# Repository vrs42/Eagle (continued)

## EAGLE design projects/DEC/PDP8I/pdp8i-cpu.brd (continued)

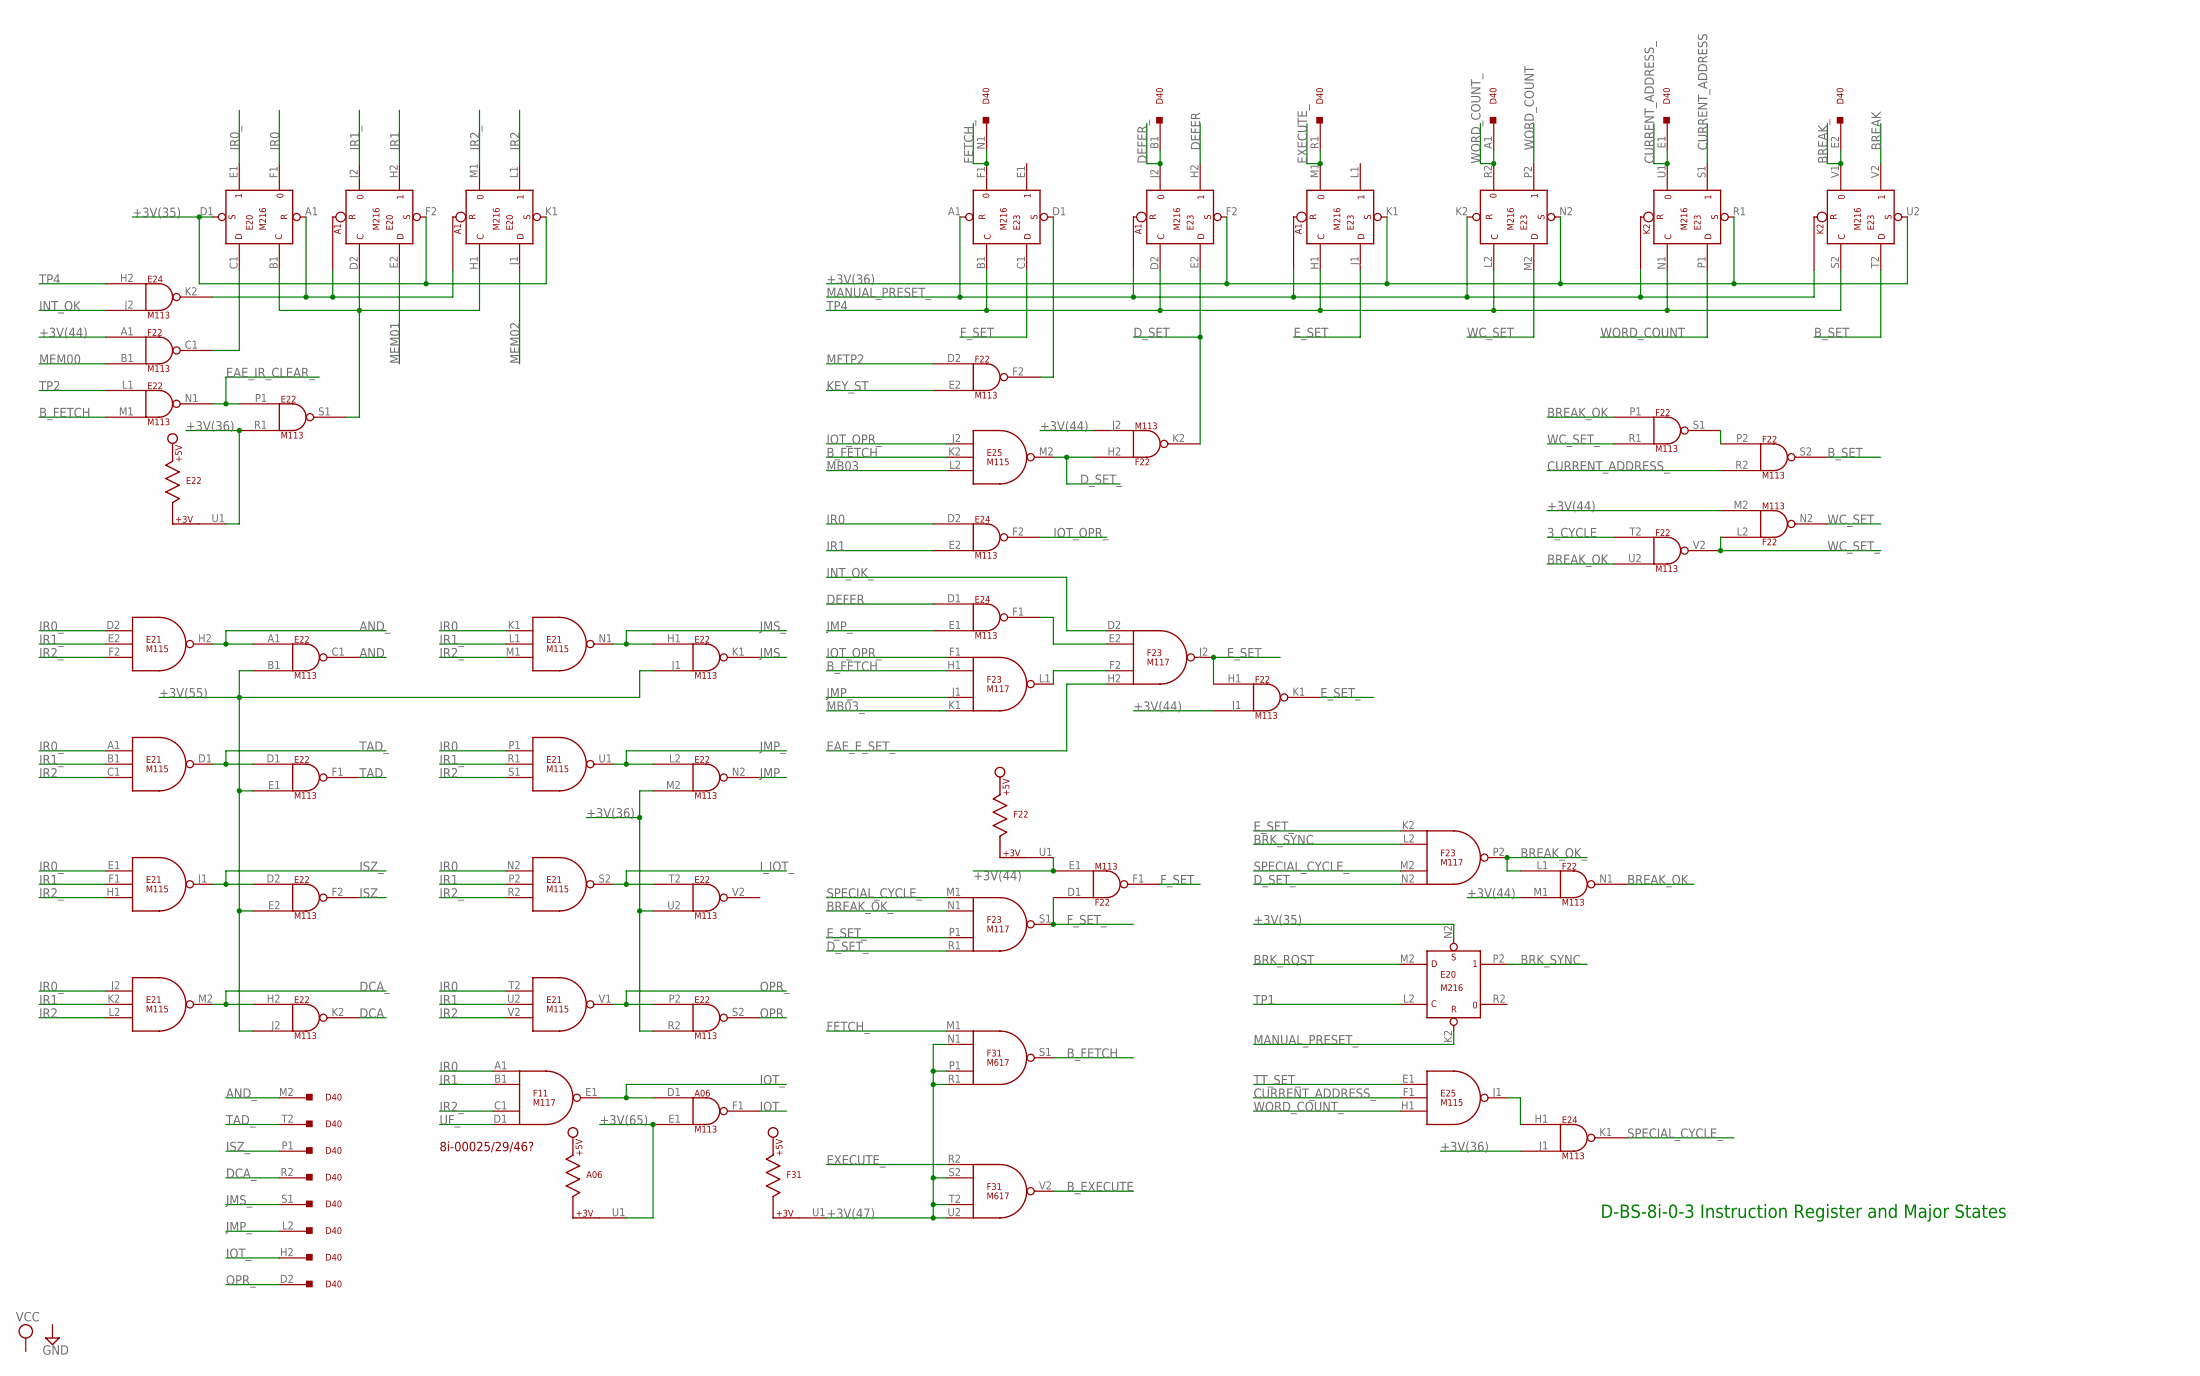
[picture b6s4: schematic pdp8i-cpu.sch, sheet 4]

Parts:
A06: M113; H807
D40: M900; H807
E20, E23: M216; H807
E21, E25: M115; H807
E22, E24: M113; H807
F11, F23: M117; H807
F22: M113; H807
F31: M617; H807

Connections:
3_CYCLE: F22.T2 (IN1); also elsewhere on the board
+3V(35): E20.D1 (S), E20.F2 (S), E20.K1 (S), E20.N2 (S); also elsewhere on the board
+3V(36): E22.M2 (IN2), E22.R1 (IN2), E22.R2 (IN2), E22.U1, E22.U2 (IN2), E23.F2 (S), E23.K1 (S), E23.N2 (S), E23.R1 (S), E23.U2 (S), E24.J1 (IN2); also elsewhere on the board
+3V(44): F22.A1 (IN1), F22.E1 (IN2), F22.J1 (IN2), F22.J2 (IN2), F22.M1 (IN2), F22.M2 (IN2), F22.U1; also elsewhere on the board
+3V(47): F31.N1 (IN2), F31.P1 (IN3), F31.R1 (IN4), F31.S2 (IN2), F31.T2 (IN3), F31.U1, F31.U2 (IN4); also elsewhere on the board
+3V(55): E22.B1 (IN2), E22.E1 (IN2), E22.E2 (IN2), E22.J1 (IN2), E22.J2 (IN2); also elsewhere on the board
+3V(65): A06.E1 (IN2), A06.U1; also elsewhere on the board
AND: E22.C1 (OUT); also elsewhere on the board
AND_: D40.M2, E21.H2 (OUT), E22.A1 (IN1); also elsewhere on the board
BREAK: E23.V2 (1); also elsewhere on the board
BREAK_: D40.E2, E23.V1 (0); also elsewhere on the board
BREAK_OK: F22.N1 (OUT), F22.P1 (IN1), F22.U2 (IN2); also elsewhere on the board
BREAK_OK_: F22.L1 (IN1), F23.N1 (IN2), F23.P2 (OUT); also elsewhere on the board
BRK_RQST: E20.M2 (D); also elsewhere on the board
BRK_SYNC: E20.P2 (1), F23.L2 (IN2)
B_EXECUTE: F31.V2 (OUT); also elsewhere on the board
B_FETCH: E22.M1 (IN2), E25.K2 (IN2), F23.H1 (IN2), F31.S1 (OUT); also elsewhere on the board
B_SET: E23.T2 (D), F22.S2 (OUT); also elsewhere on the board
CURRENT_ADDRESS: E23.S1 (1); also elsewhere on the board
CURRENT_ADDRESS_: D40.E1, E23.U1 (0), E25.F1 (IN2), F22.R2 (IN2)
DCA: E22.K2 (OUT); also elsewhere on the board
DCA_: D40.R2, E21.M2 (OUT), E22.H2 (IN1); also elsewhere on the board
DEFER: E23.H2 (1), E24.D1 (IN1); also elsewhere on the board
DEFER_: D40.B1, E23.J2 (0)
D_SET: E23.E2 (D), F22.K2 (OUT)
D_SET_: E25.M2 (OUT), F22.H2 (IN1), F23.N2 (IN4), F23.R1 (IN4); also elsewhere on the board
EAE_E_SET_: F23.H2 (IN4); also elsewhere on the board
EAE_IR_CLEAR_: E22.N1 (OUT), E22.P1 (IN1); also elsewhere on the board
EXECUTE_: D40.R1, E23.M1 (0), F31.R2 (IN1)
E_SET: E23.J1 (D), F22.H1 (IN1), F23.J2 (OUT)
E_SET_: F22.K1 (OUT), F23.K2 (IN1), F23.P1 (IN3); also elsewhere on the board
FETCH_: D40.N1, E23.F1 (0), F31.M1 (IN1); also elsewhere on the board
F_SET: E23.C1 (D), F22.F1 (OUT); also elsewhere on the board
F_SET_: F22.D1 (IN1), F23.S1 (OUT); also elsewhere on the board
GND: A06.C2 (GND), A06.T1 (GND), E20.C2 (GND), E20.T1 (GND), E21.C2 (GND), E21.T1 (GND), E22.C2 (GND), E22.T1 (GND), E23.C2 (GND), E23.T1 (GND), E24.C2 (GND), E24.T1 (GND), E25.C2 (GND), E25.T1 (GND), F11.C2 (GND), F11.T1 (GND), F22.C2 (GND), F22.T1 (GND), F23.C2 (GND), F23.T1 (GND), F31.C2 (GND), F31.T1 (GND); also elsewhere on the board
INT_OK: E24.J2 (IN2); also elsewhere on the board
INT_OK_: F23.D2 (IN1); also elsewhere on the board
IOT: A06.F1 (OUT); also elsewhere on the board
IOT_: A06.D1 (IN1), D40.H2, F11.E1 (OUT)
IOT_OPR_: E24.F2 (OUT), E25.J2 (IN1), F23.F1 (IN1)
IR0: E20.F1 (0), E21.K1 (IN1), E21.N2 (IN1), E21.P1 (IN1), E21.T2 (IN1), E24.D2 (IN1), F11.A1 (IN1)
IR0_: E20.E1 (1), E21.A1 (IN1), E21.D2 (IN1), E21.E1 (IN1), E21.J2 (IN1)
IR1: E20.H2 (1), E21.F1 (IN2), E21.K2 (IN2), E21.P2 (IN2), E21.U2 (IN2), E24.E2 (IN2), F11.B1 (IN2)
IR1_: E20.J2 (0), E21.B1 (IN2), E21.E2 (IN2), E21.L1 (IN2), E21.R1 (IN2)
IR2: E20.L1 (1), E21.C1 (IN3), E21.L2 (IN3), E21.S1 (IN3), E21.V2 (IN3)
IR2_: E20.M1 (0), E21.F2 (IN3), E21.H1 (IN3), E21.M1 (IN3), E21.R2 (IN3), F11.C1 (IN3)
ISZ: E22.F2 (OUT); also elsewhere on the board
ISZ_: D40.P1, E21.J1 (OUT), E22.D2 (IN1)
I_IOT_: E21.S2 (OUT), E22.T2 (IN1); also elsewhere on the board
JMP: E22.N2 (OUT); also elsewhere on the board
JMP_: D40.L2, E21.U1 (OUT), E22.L2 (IN1), E24.E1 (IN2), F23.J1 (IN3); also elsewhere on the board
JMS: E22.K1 (OUT); also elsewhere on the board
JMS_: D40.S1, E21.N1 (OUT), E22.H1 (IN1); also elsewhere on the board
KEY_ST: F22.E2 (IN2); also elsewhere on the board
MANUAL_PRESET_: E20.K2 (R), E23.A1 (R), E23.K2 (R); also elsewhere on the board
MB03: E25.L2 (IN3); also elsewhere on the board
MB03_: F23.K1 (IN4); also elsewhere on the board
MEM00: F22.B1 (IN2); also elsewhere on the board
MEM01: E20.E2 (D); also elsewhere on the board
MEM02: E20.J1 (D); also elsewhere on the board
MFTP2: F22.D2 (IN1); also elsewhere on the board
unnamed: E20.A1 (R), E24.K2 (OUT)
unnamed: E20.C1 (D), F22.C1 (OUT)
unnamed: E20.B1 (C), E20.D2 (C), E20.H1 (C), E22.S1 (OUT)
unnamed: E23.D1 (S), F22.F2 (OUT)
unnamed: E24.F1 (OUT), F23.E2 (IN2)
unnamed: F23.F2 (IN3), F23.L1 (OUT)
unnamed: F22.P2 (IN1), F22.S1 (OUT)
unnamed: E24.H1 (IN1), E25.J1 (OUT)
OPR: E22.S2 (OUT); also elsewhere on the board
OPR_: D40.D2, E21.V1 (OUT), E22.P2 (IN1)
SPECIAL_CYCLE_: E24.K1 (OUT), F23.M1 (IN1), F23.M2 (IN3)
TAD: E22.F1 (OUT); also elsewhere on the board
TAD_: D40.T2, E21.D1 (OUT), E22.D1 (IN1); also elsewhere on the board
TP1: E20.L2 (C); also elsewhere on the board
TP2: E22.L1 (IN1); also elsewhere on the board
TP4: E23.B1 (C), E23.D2 (C), E23.H1 (C), E23.L2 (C), E23.N1 (C), E23.S2 (C), E24.H2 (IN1); also elsewhere on the board
TT_SET_: E25.E1 (IN1); also elsewhere on the board
UF_: F11.D1 (IN4); also elsewhere on the board
VCC: A06.A2 (VCC), E20.A2 (VCC), E21.A2 (VCC), E22.A2 (VCC), E23.A2 (VCC), E24.A2 (VCC), E25.A2 (VCC), F11.A2 (VCC), F22.A2 (VCC), F23.A2 (VCC), F31.A2 (VCC); also elsewhere on the board
WC_SET: E23.M2 (D), F22.N2 (OUT)
WC_SET_: F22.L2 (IN1), F22.R1 (IN2), F22.V2 (OUT); also elsewhere on the board
WORD_COUNT: E23.P1 (D), E23.P2 (1); also elsewhere on the board
WORD_COUNT_: D40.A1, E23.R2 (0), E25.H1 (IN3); also elsewhere on the board

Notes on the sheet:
D-BS-8i-0-3 Instruction Register and Major States
8i-00025/29/46?

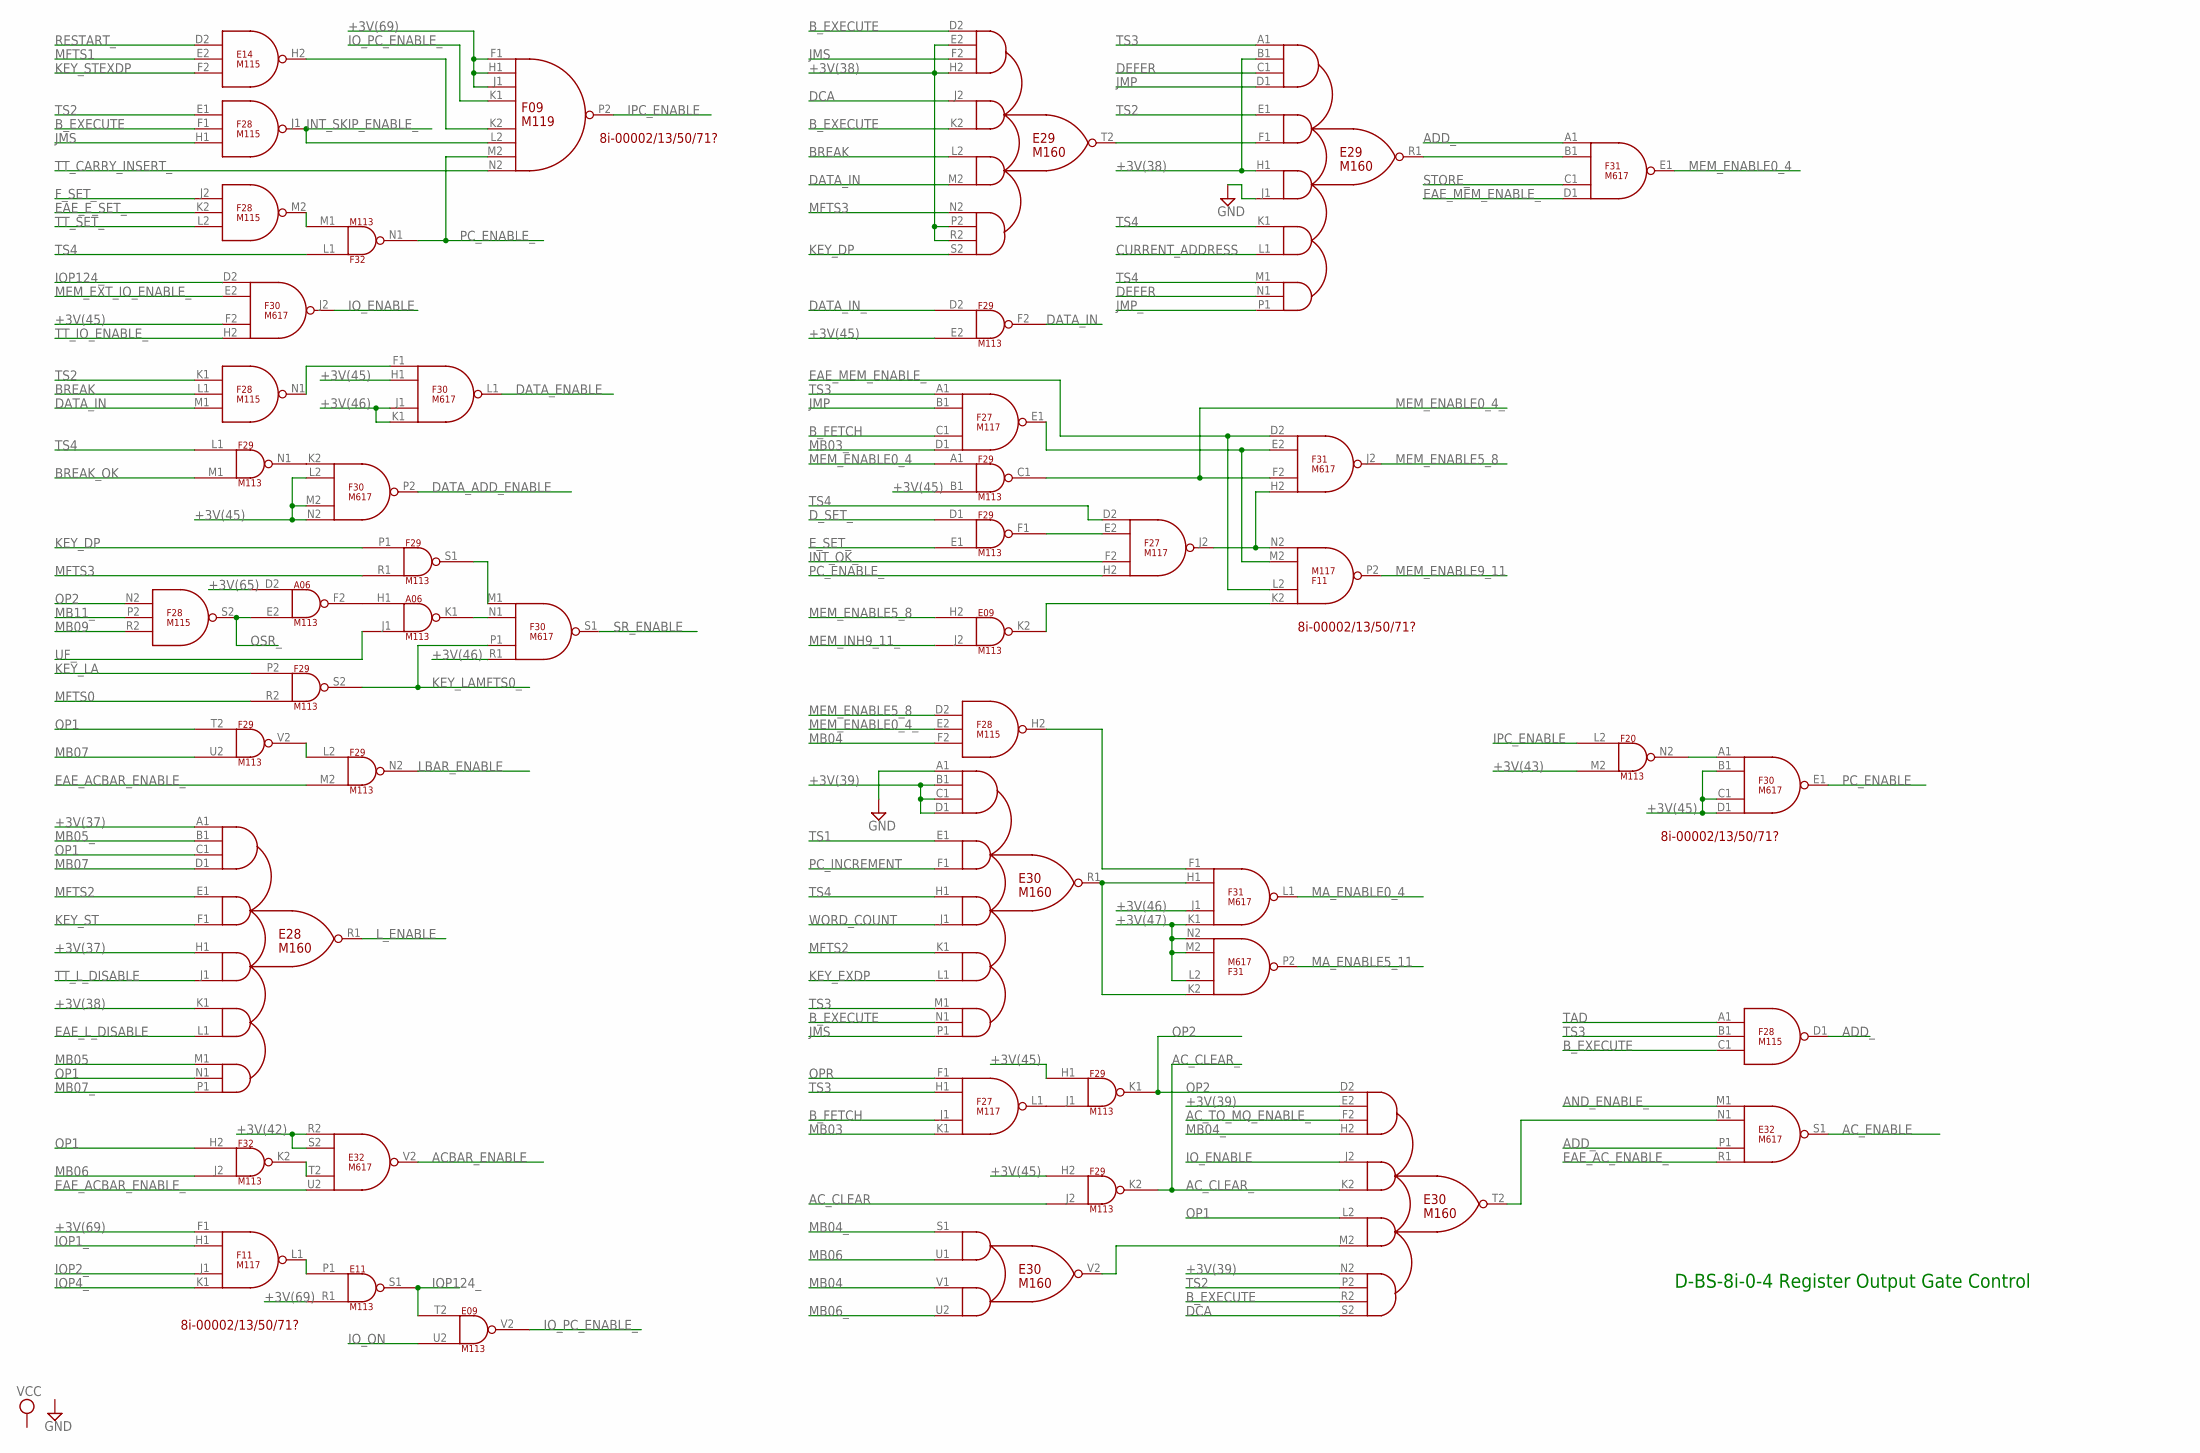
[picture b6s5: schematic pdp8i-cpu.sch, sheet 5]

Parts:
A06: M113; H807
E09, E11: M113; H807
E14: M115; H807
E28, E29, E30: M160; H807
E32: M617; H807
F09: M119; H807
F11, F27: M117; H807
F20, F29, F32: M113; H807
F28: M115; H807
F30, F31: M617; H807

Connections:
+3V(37): E28.A1 (IN1A), E28.H1 (IN3A); also elsewhere on the board
+3V(38): E28.K1 (IN4A), E29.B1 (IN1B), E29.E2 (IN1B), E29.H1 (IN3A), E29.H2 (IN1D), E29.P2 (IN4B), E29.R2 (IN4C); also elsewhere on the board
+3V(39): E30.B1 (IN1B), E30.C1 (IN1C), E30.D1 (IN1D), E30.E2 (IN1B), E30.N2 (IN4A); also elsewhere on the board
+3V(42): E32.R2 (IN1), E32.S2 (IN2); also elsewhere on the board
+3V(43): F20.M2 (IN2); also elsewhere on the board
+3V(45): F29.B1 (IN2), F29.E2 (IN2), F29.H1 (IN1), F29.H2 (IN1), F30.B1 (IN2), F30.C1 (IN3), F30.D1 (IN4), F30.F2 (IN3), F30.H1 (IN2), F30.L2 (IN2), F30.M2 (IN3), F30.N2 (IN4); also elsewhere on the board
+3V(46): F30.J1 (IN3), F30.K1 (IN4), F30.R1 (IN4), F31.J1 (IN3); also elsewhere on the board
+3V(47): F31.K1 (IN4), F31.L2 (IN2), F31.M2 (IN3), F31.N2 (IN4); also elsewhere on the board
+3V(65): A06.D2 (IN1); also elsewhere on the board
+3V(69): E11.R1 (IN2), F09.F1 (IN1), F09.H1 (IN2), F09.J1 (IN3), F11.F1 (IN1); also elsewhere on the board
ACBAR_ENABLE: E32.V2 (OUT); also elsewhere on the board
AC_CLEAR: F29.J2 (IN2); also elsewhere on the board
AC_CLEAR_: E30.K2 (IN2B), F29.K2 (OUT)
AC_ENABLE: E32.S1 (OUT); also elsewhere on the board
AC_TO_MQ_ENABLE_: E30.F2 (IN1C); also elsewhere on the board
ADD_: E32.P1 (IN3), F28.D1 (OUT), F31.A1 (IN1)
AND_ENABLE_: E32.M1 (IN1); also elsewhere on the board
BREAK: E29.L2 (IN3A), F28.L1 (IN2); also elsewhere on the board
BREAK_OK: F29.M1 (IN2); also elsewhere on the board
B_EXECUTE: E29.D2 (IN1A), E29.K2 (IN2B), E30.N1 (IN5B), E30.R2 (IN4C), F28.C1 (IN3), F28.F1 (IN2); also elsewhere on the board
B_FETCH: F27.C1 (IN3), F27.J1 (IN3); also elsewhere on the board
CURRENT_ADDRESS: E29.L1 (IN4B); also elsewhere on the board
DATA_ADD_ENABLE: F30.P2 (OUT); also elsewhere on the board
DATA_ENABLE: F30.L1 (OUT); also elsewhere on the board
DATA_IN: E29.M2 (IN3B), F28.M1 (IN3), F29.F2 (OUT)
DATA_IN_: F29.D2 (IN1); also elsewhere on the board
DCA: E29.J2 (IN2A), E30.S2 (IN4D); also elsewhere on the board
DEFER: E29.C1 (IN1C), E29.N1 (IN5B); also elsewhere on the board
D_SET_: F29.D1 (IN1); also elsewhere on the board
EAE_ACBAR_ENABLE_: E32.U2 (IN4), F29.M2 (IN2); also elsewhere on the board
EAE_AC_ENABLE_: E32.R1 (IN4); also elsewhere on the board
EAE_E_SET_: F28.K2 (IN2); also elsewhere on the board
EAE_L_DISABLE: E28.L1 (IN4B); also elsewhere on the board
EAE_MEM_ENABLE_: F11.L2 (IN2), F31.D1 (IN4), F31.D2 (IN1); also elsewhere on the board
E_SET_: F29.E1 (IN2); also elsewhere on the board
F_SET_: F28.J2 (IN1); also elsewhere on the board
GND: A06.C2 (GND), A06.T1 (GND), E09.C2 (GND), E09.T1 (GND), E11.C2 (GND), E11.T1 (GND), E14.C2 (GND), E14.T1 (GND), E28.C2 (GND), E28.T1 (GND), E29.C2 (GND), E29.J1 (IN3B), E29.T1 (GND), E30.A1 (IN1A), E30.C2 (GND), E30.T1 (GND), E32.C2 (GND), E32.T1 (GND), F09.C2 (GND), F09.T1 (GND), F11.C2 (GND), F11.T1 (GND), F20.C2 (GND), F20.T1 (GND), F27.C2 (GND), F27.T1 (GND), F28.C2 (GND), F28.T1 (GND), F29.C2 (GND), F29.T1 (GND), F30.C2 (GND), F30.T1 (GND), F31.C2 (GND), F31.T1 (GND), F32.C2 (GND), F32.T1 (GND); also elsewhere on the board
INT_OK_: F27.F2 (IN3); also elsewhere on the board
INT_SKIP_ENABLE_: F09.L2 (IN6), F28.J1 (OUT); also elsewhere on the board
IOP1_: F11.H1 (IN2); also elsewhere on the board
IOP2_: F11.J1 (IN3); also elsewhere on the board
IOP4_: F11.K1 (IN4); also elsewhere on the board
IOP124_: E09.T2 (IN1), E11.S1 (OUT), F30.D2 (IN1)
IO_ENABLE: E30.J2 (IN2A), F30.J2 (OUT); also elsewhere on the board
IO_ON: E09.U2 (IN2); also elsewhere on the board
IO_PC_ENABLE_: E09.V2 (OUT), F09.K1 (IN4); also elsewhere on the board
IPC_ENABLE: F09.P2 (OUT), F20.L2 (IN1)
JMP: E29.D1 (IN1D), F27.B1 (IN2); also elsewhere on the board
JMP_: E29.P1 (IN5C); also elsewhere on the board
JMS: E29.F2 (IN1C), E30.P1 (IN5C), F28.H1 (IN3); also elsewhere on the board
KEY_DP: E29.S2 (IN4D), F29.P1 (IN1); also elsewhere on the board
KEY_EXDP: E30.L1 (IN4B); also elsewhere on the board
KEY_LA: F29.P2 (IN1); also elsewhere on the board
KEY_LAMFTS0_: F29.S2 (OUT), F30.P1 (IN3); also elsewhere on the board
KEY_ST: E28.F1 (IN2B); also elsewhere on the board
KEY_STEXDP: E14.F2 (IN3); also elsewhere on the board
LBAR_ENABLE: F29.N2 (OUT); also elsewhere on the board
L_ENABLE: E28.R1 (OUT); also elsewhere on the board
MA_ENABLE0_4: F31.L1 (OUT); also elsewhere on the board
MA_ENABLE5_11: F31.P2 (OUT); also elsewhere on the board
MB03: F27.K1 (IN4); also elsewhere on the board
MB03_: F27.D1 (IN4); also elsewhere on the board
MB04: E30.V1 (IN2A), F28.F2 (IN3); also elsewhere on the board
MB04_: E30.H2 (IN1D), E30.S1 (IN1A); also elsewhere on the board
MB05: E28.M1 (IN5A); also elsewhere on the board
MB05_: E28.B1 (IN1B); also elsewhere on the board
MB06: E30.U1 (IN1B), F32.J2 (IN2); also elsewhere on the board
MB06_: E30.U2 (IN2B); also elsewhere on the board
MB07: E28.D1 (IN1D), F29.U2 (IN2); also elsewhere on the board
MB07_: E28.P1 (IN5C); also elsewhere on the board
MB09: F28.R2 (IN3); also elsewhere on the board
MB11_: F28.P2 (IN2); also elsewhere on the board
MEM_ENABLE0_4: F29.A1 (IN1), F31.E1 (OUT); also elsewhere on the board
MEM_ENABLE0_4_: F28.E2 (IN2), F29.C1 (OUT), F31.F2 (IN3)
MEM_ENABLE5_8: E09.H2 (IN1), F28.D2 (IN1), F31.J2 (OUT); also elsewhere on the board
MEM_ENABLE9_11: F11.P2 (OUT); also elsewhere on the board
MEM_EXT_IO_ENABLE_: F30.E2 (IN2); also elsewhere on the board
MEM_INH9_11_: E09.J2 (IN2); also elsewhere on the board
MFTS0: F29.R2 (IN2); also elsewhere on the board
MFTS1: E14.E2 (IN2); also elsewhere on the board
MFTS2: E28.E1 (IN2A), E30.K1 (IN4A); also elsewhere on the board
MFTS3: E29.N2 (IN4A), F29.R1 (IN2); also elsewhere on the board
unnamed: E29.R1 (OUT), F31.B1 (IN2)
unnamed: E09.K2 (OUT), F11.K2 (IN1)
unnamed: F27.E2 (IN2), F29.F1 (OUT)
unnamed: F11.M2 (IN3), F27.E1 (OUT), F31.E2 (IN2)
unnamed: E30.R1 (OUT), F31.H1 (IN2), F31.K2 (IN1)
unnamed: A06.F2 (OUT), A06.H1 (IN1)
unnamed: E14.H2 (OUT), F09.K2 (IN5)
unnamed: F28.M2 (OUT), F32.M1 (IN2)
unnamed: F29.L2 (IN1), F29.V2 (OUT)
unnamed: F28.N1 (OUT), F30.F1 (IN1)
unnamed: E29.F1 (IN2B), E29.T2 (OUT)
unnamed: F29.N1 (OUT), F30.K2 (IN1)
unnamed: A06.K1 (OUT), F30.N1 (IN2)
unnamed: F29.S1 (OUT), F30.M1 (IN1)
unnamed: E32.T2 (IN3), F32.K2 (OUT)
unnamed: F11.N2 (IN4), F27.J2 (OUT), F31.H2 (IN4)
unnamed: F28.H2 (OUT), F31.F1 (IN1)
unnamed: F27.L1 (OUT), F29.J1 (IN2)
unnamed: E30.T2 (OUT), E32.N1 (IN2)
unnamed: E30.M2 (IN3B), E30.V2 (OUT)
unnamed: E11.P1 (IN1), F11.L1 (OUT)
unnamed: F20.N2 (OUT), F30.A1 (IN1)
OP1: E28.C1 (IN1C), E28.N1 (IN5B), E30.L2 (IN3A), F29.T2 (IN1), F32.H2 (IN1); also elsewhere on the board
OP2: E30.D2 (IN1A), F28.N2 (IN1), F29.K1 (OUT); also elsewhere on the board
OPR: F27.F1 (IN1); also elsewhere on the board
OSR_: A06.E2 (IN2), F28.S2 (OUT)
PC_ENABLE: F30.E1 (OUT); also elsewhere on the board
PC_ENABLE_: F09.M2 (IN7), F27.H2 (IN4), F32.N1 (OUT); also elsewhere on the board
PC_INCREMENT: E30.F1 (IN2B); also elsewhere on the board
RESTART_: E14.D2 (IN1); also elsewhere on the board
SR_ENABLE: F30.S1 (OUT); also elsewhere on the board
STORE_: F31.C1 (IN3); also elsewhere on the board
TAD: F28.A1 (IN1); also elsewhere on the board
TS1: E30.E1 (IN2A); also elsewhere on the board
TS2: E29.E1 (IN2A), E30.P2 (IN4B), F28.E1 (IN1), F28.K1 (IN1); also elsewhere on the board
TS3: E29.A1 (IN1A), E30.M1 (IN5A), F27.A1 (IN1), F27.H1 (IN2), F28.B1 (IN2); also elsewhere on the board
TS4: E29.K1 (IN4A), E29.M1 (IN5A), E30.H1 (IN3A), F27.D2 (IN1), F29.L1 (IN1), F32.L1 (IN1); also elsewhere on the board
TT_CARRY_INSERT_: F09.N2 (IN8); also elsewhere on the board
TT_IO_ENABLE_: F30.H2 (IN4); also elsewhere on the board
TT_L_DISABLE: E28.J1 (IN3B); also elsewhere on the board
TT_SET_: F28.L2 (IN3); also elsewhere on the board
UF_: A06.J1 (IN2); also elsewhere on the board
VCC: A06.A2 (VCC), E09.A2 (VCC), E11.A2 (VCC), E14.A2 (VCC), E28.A2 (VCC), E29.A2 (VCC), E30.A2 (VCC), E32.A2 (VCC), F09.A2 (VCC), F11.A2 (VCC), F20.A2 (VCC), F27.A2 (VCC), F28.A2 (VCC), F29.A2 (VCC), F30.A2 (VCC), F31.A2 (VCC), F32.A2 (VCC); also elsewhere on the board
WORD_COUNT: E30.J1 (IN3B); also elsewhere on the board

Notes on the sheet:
D-BS-8i-0-4 Register Output Gate Control
8i-00002/13/50/71?

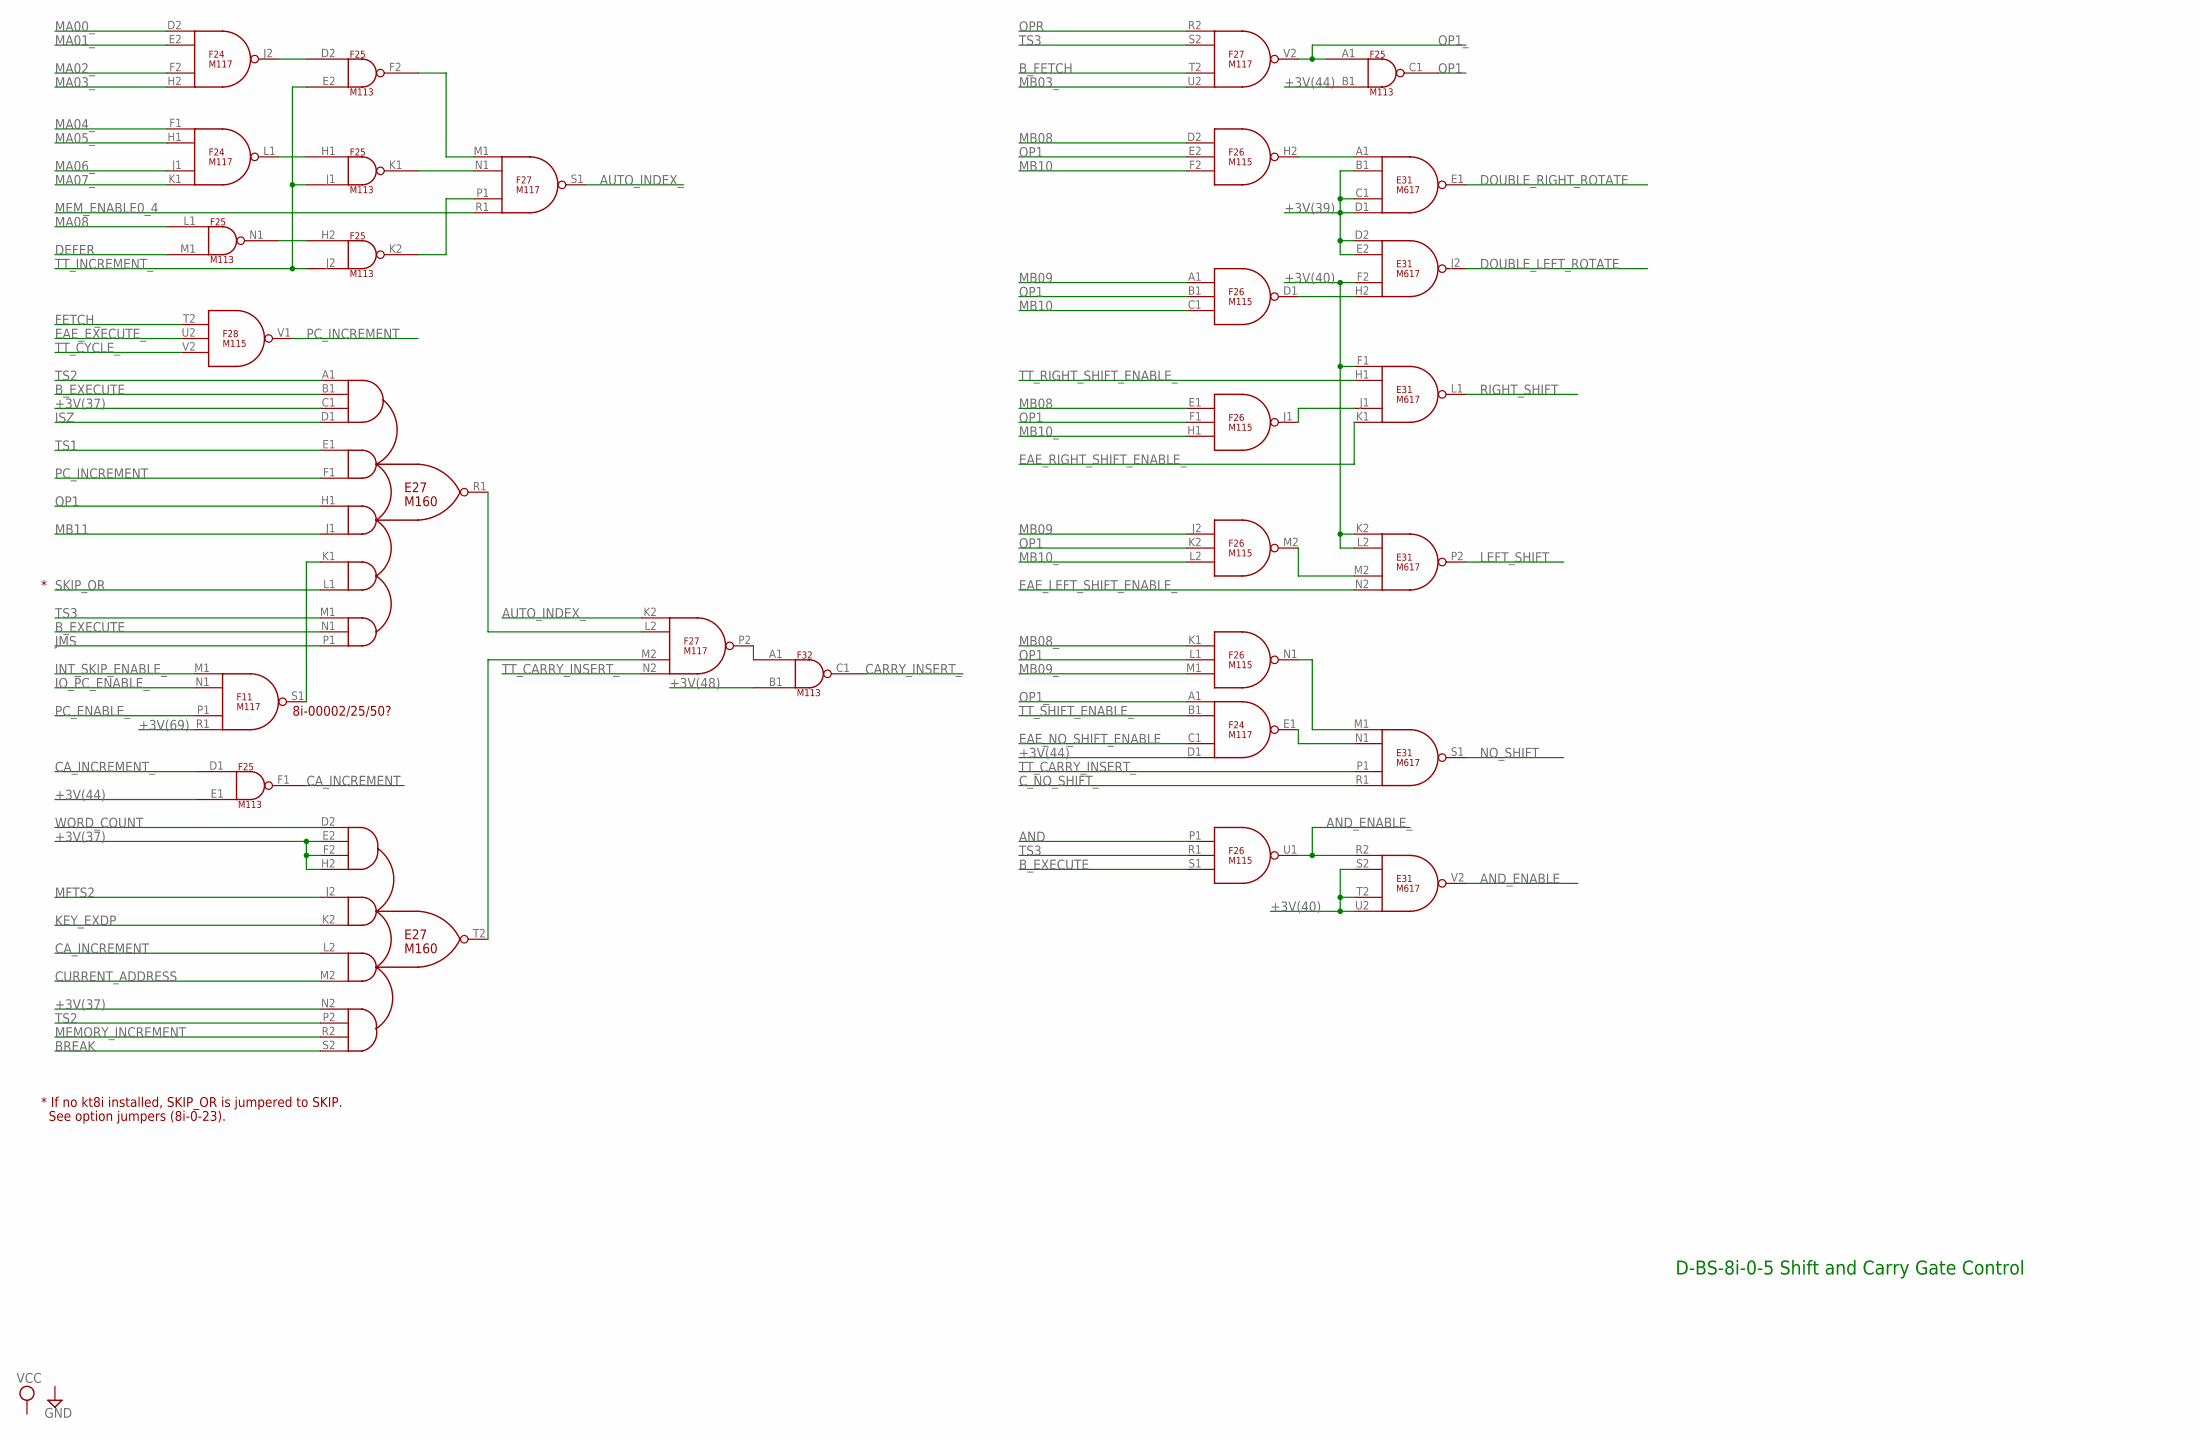
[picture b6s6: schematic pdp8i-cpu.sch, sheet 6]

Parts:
E27: M160; H807
E31: M617; H807
F11, F24, F27: M117; H807
F25, F32: M113; H807
F26, F28: M115; H807

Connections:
+3V(37): E27.C1 (IN1C), E27.E2 (IN1B), E27.F2 (IN1C), E27.H2 (IN1D), E27.N2 (IN4A); also elsewhere on the board
+3V(39): E31.B1 (IN2), E31.C1 (IN3), E31.D1 (IN4), E31.D2 (IN1), E31.E2 (IN2); also elsewhere on the board
+3V(40): E31.F1 (IN1), E31.F2 (IN3), E31.K2 (IN1), E31.L2 (IN2), E31.S2 (IN2), E31.T2 (IN3), E31.U2 (IN4); also elsewhere on the board
+3V(44): F24.D1 (IN4), F25.B1 (IN2), F25.E1 (IN2); also elsewhere on the board
+3V(48): F32.B1 (IN2); also elsewhere on the board
+3V(69): F11.R1 (IN4); also elsewhere on the board
AND: F26.P1 (IN1); also elsewhere on the board
AND_ENABLE: E31.V2 (OUT); also elsewhere on the board
AND_ENABLE_: E31.R2 (IN1), F26.U1 (OUT); also elsewhere on the board
AUTO_INDEX_: F27.K2 (IN1), F27.S1 (OUT)
BREAK: E27.S2 (IN4D); also elsewhere on the board
B_EXECUTE: E27.B1 (IN1B), E27.N1 (IN5B), F26.S1 (IN3); also elsewhere on the board
B_FETCH: F27.T2 (IN3); also elsewhere on the board
CARRY_INSERT_: F32.C1 (OUT); also elsewhere on the board
CA_INCREMENT: E27.L2 (IN3A), F25.F1 (OUT)
CA_INCREMENT_: F25.D1 (IN1); also elsewhere on the board
CURRENT_ADDRESS: E27.M2 (IN3B); also elsewhere on the board
C_NO_SHIFT_: E31.R1 (IN4); also elsewhere on the board
DEFER: F25.M1 (IN2); also elsewhere on the board
DOUBLE_LEFT_ROTATE: E31.J2 (OUT); also elsewhere on the board
DOUBLE_RIGHT_ROTATE: E31.E1 (OUT); also elsewhere on the board
EAE_EXECUTE_: F28.U2 (IN2); also elsewhere on the board
EAE_LEFT_SHIFT_ENABLE_: E31.N2 (IN4); also elsewhere on the board
EAE_NO_SHIFT_ENABLE: F24.C1 (IN3); also elsewhere on the board
EAE_RIGHT_SHIFT_ENABLE_: E31.K1 (IN4); also elsewhere on the board
FETCH_: F28.T2 (IN1); also elsewhere on the board
GND: E27.C2 (GND), E27.T1 (GND), E31.C2 (GND), E31.T1 (GND), F11.C2 (GND), F11.T1 (GND), F24.C2 (GND), F24.T1 (GND), F25.C2 (GND), F25.T1 (GND), F26.C2 (GND), F26.T1 (GND), F27.C2 (GND), F27.T1 (GND), F28.C2 (GND), F28.T1 (GND), F32.C2 (GND), F32.T1 (GND); also elsewhere on the board
INT_SKIP_ENABLE_: F11.M1 (IN1); also elsewhere on the board
IO_PC_ENABLE_: F11.N1 (IN2); also elsewhere on the board
ISZ: E27.D1 (IN1D); also elsewhere on the board
JMS: E27.P1 (IN5C); also elsewhere on the board
KEY_EXDP: E27.K2 (IN2B); also elsewhere on the board
LEFT_SHIFT: E31.P2 (OUT); also elsewhere on the board
MA00_: F24.D2 (IN1); also elsewhere on the board
MA01_: F24.E2 (IN2); also elsewhere on the board
MA02_: F24.F2 (IN3); also elsewhere on the board
MA03_: F24.H2 (IN4); also elsewhere on the board
MA04_: F24.F1 (IN1); also elsewhere on the board
MA05_: F24.H1 (IN2); also elsewhere on the board
MA06_: F24.J1 (IN3); also elsewhere on the board
MA07_: F24.K1 (IN4); also elsewhere on the board
MA08: F25.L1 (IN1); also elsewhere on the board
MB03_: F27.U2 (IN4); also elsewhere on the board
MB08: F26.D2 (IN1), F26.E1 (IN1); also elsewhere on the board
MB08_: F26.K1 (IN1); also elsewhere on the board
MB09: F26.A1 (IN1), F26.J2 (IN1); also elsewhere on the board
MB09_: F26.M1 (IN3); also elsewhere on the board
MB10: F26.C1 (IN3), F26.F2 (IN3); also elsewhere on the board
MB10_: F26.H1 (IN3), F26.L2 (IN3); also elsewhere on the board
MB11: E27.J1 (IN3B); also elsewhere on the board
MEMORY_INCREMENT: E27.R2 (IN4C); also elsewhere on the board
MEM_ENABLE0_4: F27.R1 (IN4); also elsewhere on the board
MFTS2: E27.J2 (IN2A); also elsewhere on the board
unnamed: F25.H2 (IN1), F25.N1 (OUT)
unnamed: F24.L1 (OUT), F25.H1 (IN1)
unnamed: F24.J2 (OUT), F25.D2 (IN1)
unnamed: E27.K1 (IN4A), F11.S1 (OUT)
unnamed: E27.T2 (OUT), F27.M2 (IN3)
unnamed: E27.R1 (OUT), F27.L2 (IN2)
unnamed: E31.N1 (IN2), F24.E1 (OUT)
unnamed: F25.K2 (OUT), F27.P1 (IN3)
unnamed: F25.K1 (OUT), F27.N1 (IN2)
unnamed: F25.F2 (OUT), F27.M1 (IN1)
unnamed: E31.M1 (IN1), F26.N1 (OUT)
unnamed: F27.P2 (OUT), F32.A1 (IN1)
unnamed: E31.H2 (IN4), F26.D1 (OUT)
unnamed: E31.J1 (IN3), F26.J1 (OUT)
unnamed: E31.M2 (IN3), F26.M2 (OUT)
unnamed: E31.A1 (IN1), F26.H2 (OUT)
NO_SHIFT: E31.S1 (OUT); also elsewhere on the board
OP1: E27.H1 (IN3A), F25.C1 (OUT), F26.B1 (IN2), F26.E2 (IN2), F26.F1 (IN2), F26.K2 (IN2), F26.L1 (IN2); also elsewhere on the board
OP1_: F24.A1 (IN1), F25.A1 (IN1), F27.V2 (OUT)
OPR: F27.R2 (IN1); also elsewhere on the board
PC_ENABLE_: F11.P1 (IN3); also elsewhere on the board
PC_INCREMENT: E27.F1 (IN2B), F28.V1 (OUT); also elsewhere on the board
RIGHT_SHIFT: E31.L1 (OUT); also elsewhere on the board
SKIP_OR: E27.L1 (IN4B); also elsewhere on the board
TS1: E27.E1 (IN2A); also elsewhere on the board
TS2: E27.A1 (IN1A), E27.P2 (IN4B); also elsewhere on the board
TS3: E27.M1 (IN5A), F26.R1 (IN2), F27.S2 (IN2); also elsewhere on the board
TT_CARRY_INSERT_: E31.P1 (IN3), F27.N2 (IN4); also elsewhere on the board
TT_CYCLE_: F28.V2 (IN3); also elsewhere on the board
TT_INCREMENT_: F25.E2 (IN2), F25.J1 (IN2), F25.J2 (IN2); also elsewhere on the board
TT_RIGHT_SHIFT_ENABLE_: E31.H1 (IN2); also elsewhere on the board
TT_SHIFT_ENABLE_: F24.B1 (IN2); also elsewhere on the board
VCC: E27.A2 (VCC), E31.A2 (VCC), F11.A2 (VCC), F24.A2 (VCC), F25.A2 (VCC), F26.A2 (VCC), F27.A2 (VCC), F28.A2 (VCC), F32.A2 (VCC); also elsewhere on the board
WORD_COUNT: E27.D2 (IN1A); also elsewhere on the board

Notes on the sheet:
D-BS-8i-0-5 Shift and Carry Gate Control
8i-00002/25/50?
* If no kt8i installed, SKIP_OR is jumpered to SKIP.
See option jumpers (8i-0-23).
